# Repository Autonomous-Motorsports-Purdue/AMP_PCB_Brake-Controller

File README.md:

# AMP_PCB_Brake-Controller
PCB with brake motor controller files and documentation

## Features
- Breakout board form factor for easy replacement
- Large maximum current rating (50A continuous, 117A pulse)
- Motor driver (currently) still in production

## Testing
- [X] Order PCB
- [X] Assemble PCB
- [ ] Test PCB independently
  - [X] Simple forward/reverse polarity
  - [X] Higher current (motor) load
  - [ ] PWM forward/reverse
  - [X] PWM motor load
- [ ] Test PCB on kart

## Notes
- Find reverse polarity protection MOSFET and suitable zener diode
  - MOSFET package: TO-252
  - Zener package: SOT-23
- Use largest 0805 capacitor for C7 (1000uF in schematic)
- To add reverse polarity protection, solder Q1, D1, R1
- To bypass reverse polarity protection, bridge JP1
- All passive components are 0805 package size

---

## Useful figures

Operation truth table:

Absolute maximum ratings:

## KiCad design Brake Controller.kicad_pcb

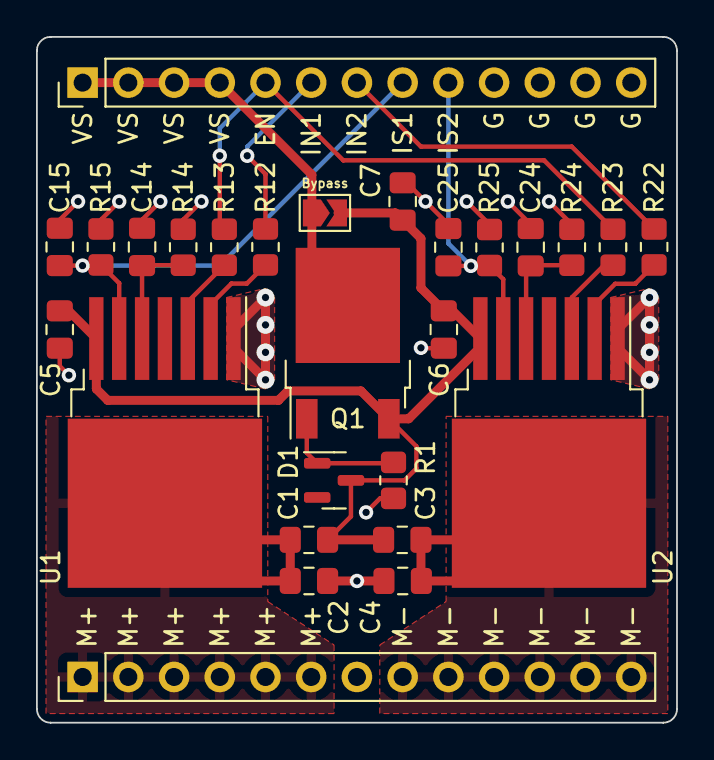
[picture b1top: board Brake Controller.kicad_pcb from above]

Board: 2 copper layers, 35.6 x 38.1 mm, 27 parts (0 on the bottom side), 17 nets.

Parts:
C1, C2, C3, C4: 220nF; C_0805_2012Metric_Pad1.18x1.45mm_HandSolder
C5, C6: 100nF; C_0805_2012Metric_Pad1.18x1.45mm_HandSolder
C7: 1000uF; C_0805_2012Metric_Pad1.18x1.45mm_HandSolder
C14, C24: 1nF; C_0805_2012Metric_Pad1.18x1.45mm_HandSolder
C15, C25: 10nF; C_0805_2012Metric_Pad1.18x1.45mm_HandSolder
D1: 10V; SOT-23
J1: INPUT; PinHeader_1x13_P2.54mm_Vertical
J2: OUTPUT; PinHeader_1x13_P2.54mm_Vertical
JP1: Protection bypass; SolderJumper-2_P1.3mm_Open_TrianglePad1.0x1.5mm
Q1: Q_PMOS_GDS; TO-252-2
R1, R12, R13, R22, R23: 10K; R_0805_2012Metric_Pad1.20x1.40mm_HandSolder
R14, R24: 500; R_0805_2012Metric_Pad1.20x1.40mm_HandSolder
R15, R25: 1K; R_0805_2012Metric_Pad1.20x1.40mm_HandSolder
U1, U2: IFX007T; TO-263-7_TabPin4

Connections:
/EN: J1.5, R13.2, R23.2
/IN1: J1.6, R12.2
/IN2: J1.7, R22.2
/IS1: C15.1, J1.8, R15.1, U1.6 (IS)
/IS2: C25.1, J1.9, R25.1, U2.6 (IS)
/MOTOR+: C1.2, C2.1, J2.1, J2.2, J2.3, J2.4, J2.5, J2.6, U1.4 (OUT)
/MOTOR-: C3.2, C4.1, J2.8, J2.9, J2.10, J2.11, J2.12, J2.13, U2.4 (OUT)
GND: C2.2, C4.2, C5.2, C6.2, C7.2, C14.2, C15.2, C24.2, C25.2, J1.10, J1.11, J1.12, J1.13, R1.2, R14.2, R15.2, R24.2, R25.2, U1.1 (GND), U2.1 (GND)
unnamed: C1.1, C3.1, C5.1, C6.1, C7.1, D1.3 (K), JP1.2 (B), Q1.3 (S), U1.7 (VS), U2.7 (VS)
unnamed: C14.1, R14.1, U1.5 (SR)
unnamed: C24.1, R24.1, U2.5 (SR)
unnamed: D1.1 (A), Q1.1 (G), R1.1
unnamed: R12.1, U1.2 (IN)
unnamed: R13.1, U1.3 (INH)
unnamed: R22.1, U2.2 (IN)
unnamed: R23.1, U2.3 (INH)
VS: J1.1, J1.2, J1.3, J1.4, JP1.1 (A), Q1.2 (D)

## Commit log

2022-04-04 Ignore backup files
2022-04-04 Initial schematic commit
2022-04-04 Add pin headers, prepare for PCB layout
2022-04-04 Edit author/schematic title
2022-04-04 Fix missing GND labels
2022-04-04 Add useful documentation
2022-04-09 Add package information
2022-04-09 Add reverse polarity bypass
2022-04-09 Add AMP logo
2022-04-09 Fix motor driver pinout
2022-04-09 Route PCB
2022-04-12 Add larger ground pour to motor driver pin 1
2022-04-22 Add thermal relief to motor controller connections
2022-05-09 Add adjustable PWM firmware
2022-05-09 Update progress checkboxes
